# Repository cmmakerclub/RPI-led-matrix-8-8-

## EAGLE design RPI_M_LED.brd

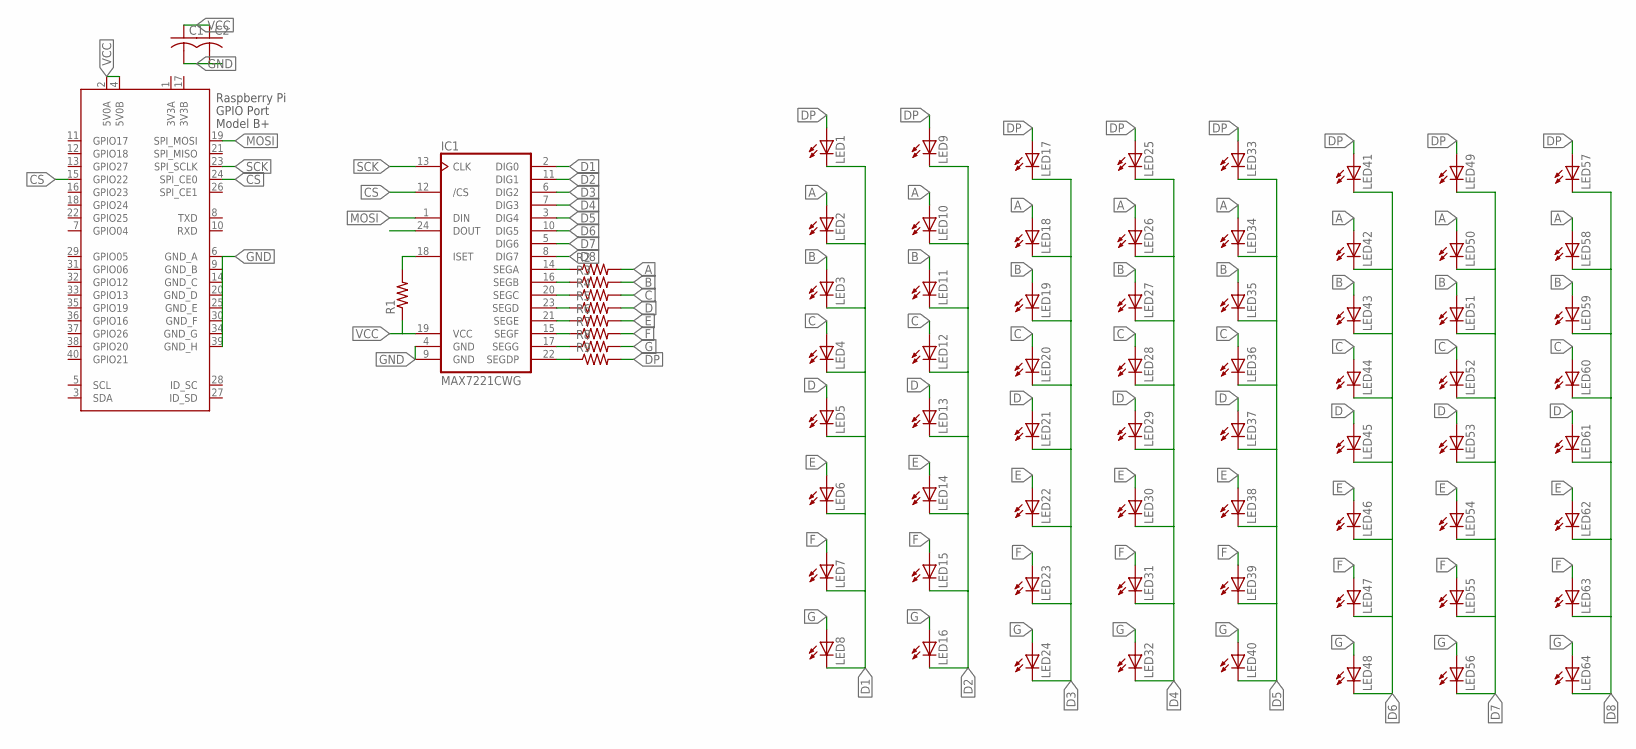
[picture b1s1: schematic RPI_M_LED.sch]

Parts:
C1, C2: C-USC0805; C0805
IC1: MAX7221CWG; SO24W
LED1, LED2, LED3, LED4, LED5, LED6, LED7, LED8, LED9, LED10, LED11, LED12, LED13, LED14, LED15, LED16, LED17, LED18, LED19, LED20, LED21, LED22, LED23, LED24, LED25, LED26, LED27, LED28, LED29, LED30, LED31, LED32, LED33, LED34, LED35, LED36, LED37, LED38, LED39, LED40, LED41, LED42, LED43, LED44, LED45, LED46, LED47, LED48, LED49, LED50, LED51, LED52, LED53, LED54, LED55, LED56, LED57, LED58, LED59, LED60, LED61, LED62, LED63, LED64: LEDCHIPLED_0603; CHIPLED_0603
R1: R-US_R0805; R0805
R2, R3, R4, R5, R6, R7, R8, R9: R-US_R0603; R0603
X1: RASPI_GPIO_B+#_PIN; RASPI_GPIO_B+_PIN

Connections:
3V3A: X1.1 (3V3A)
3V3B: X1.17 (3V3B)
A: LED2.A, LED10.A, LED18.A, LED26.A, LED34.A, LED42.A, LED50.A, LED58.A, R2.2
B: LED3.A, LED11.A, LED19.A, LED27.A, LED35.A, LED43.A, LED51.A, LED59.A, R3.2
C: LED4.A, LED12.A, LED20.A, LED28.A, LED36.A, LED44.A, LED52.A, LED60.A, R4.2
CS: IC1.12 (/CS), X1.15 (GPIO22), X1.24 (SPI_CE0)
D: LED5.A, LED13.A, LED21.A, LED29.A, LED37.A, LED45.A, LED53.A, LED61.A, R5.2
D1: IC1.2 (DIG0), LED1.C, LED2.C, LED3.C, LED4.C, LED5.C, LED6.C, LED7.C, LED8.C
D2: IC1.11 (DIG1), LED9.C, LED10.C, LED11.C, LED12.C, LED13.C, LED14.C, LED15.C, LED16.C
D3: IC1.6 (DIG2), LED17.C, LED18.C, LED19.C, LED20.C, LED21.C, LED22.C, LED23.C, LED24.C
D4: IC1.7 (DIG3), LED25.C, LED26.C, LED27.C, LED28.C, LED29.C, LED30.C, LED31.C, LED32.C
D5: IC1.3 (DIG4), LED33.C, LED34.C, LED35.C, LED36.C, LED37.C, LED38.C, LED39.C, LED40.C
D6: IC1.10 (DIG5), LED41.C, LED42.C, LED43.C, LED44.C, LED45.C, LED46.C, LED47.C, LED48.C
D7: IC1.5 (DIG6), LED49.C, LED50.C, LED51.C, LED52.C, LED53.C, LED54.C, LED55.C, LED56.C
D8: IC1.8 (DIG7), LED57.C, LED58.C, LED59.C, LED60.C, LED61.C, LED62.C, LED63.C, LED64.C
DP: LED1.A, LED9.A, LED17.A, LED25.A, LED33.A, LED41.A, LED49.A, LED57.A, R9.2
E: LED6.A, LED14.A, LED22.A, LED30.A, LED38.A, LED46.A, LED54.A, LED62.A, R6.2
F: LED7.A, LED15.A, LED23.A, LED31.A, LED39.A, LED47.A, LED55.A, LED63.A, R7.2
G: LED8.A, LED16.A, LED24.A, LED32.A, LED40.A, LED48.A, LED56.A, LED64.A, R8.2
GND: C1.2, C2.2, IC1.4 (GND), IC1.9 (GND), X1.6 (GND_A), X1.9 (GND_B), X1.14 (GND_C), X1.20 (GND_D), X1.25 (GND_E), X1.30 (GND_F), X1.34 (GND_G), X1.39 (GND_H)
MOSI: IC1.1 (DIN), X1.19 (SPI_MOSI)
unnamed: IC1.14 (SEGA), R2.1
unnamed: IC1.16 (SEGB), R3.1
unnamed: IC1.20 (SEGC), R4.1
unnamed: IC1.23 (SEGD), R5.1
unnamed: IC1.21 (SEGE), R6.1
unnamed: IC1.18 (ISET), R1.2
unnamed: IC1.15 (SEGF), R7.1
unnamed: IC1.17 (SEGG), R8.1
unnamed: IC1.22 (SEGDP), R9.1
SCK: IC1.13 (CLK), X1.23 (SPI_SCLK)
VCC: C1.1, C2.1, IC1.19 (VCC), R1.1, X1.2 (5V0A), X1.4 (5V0B)

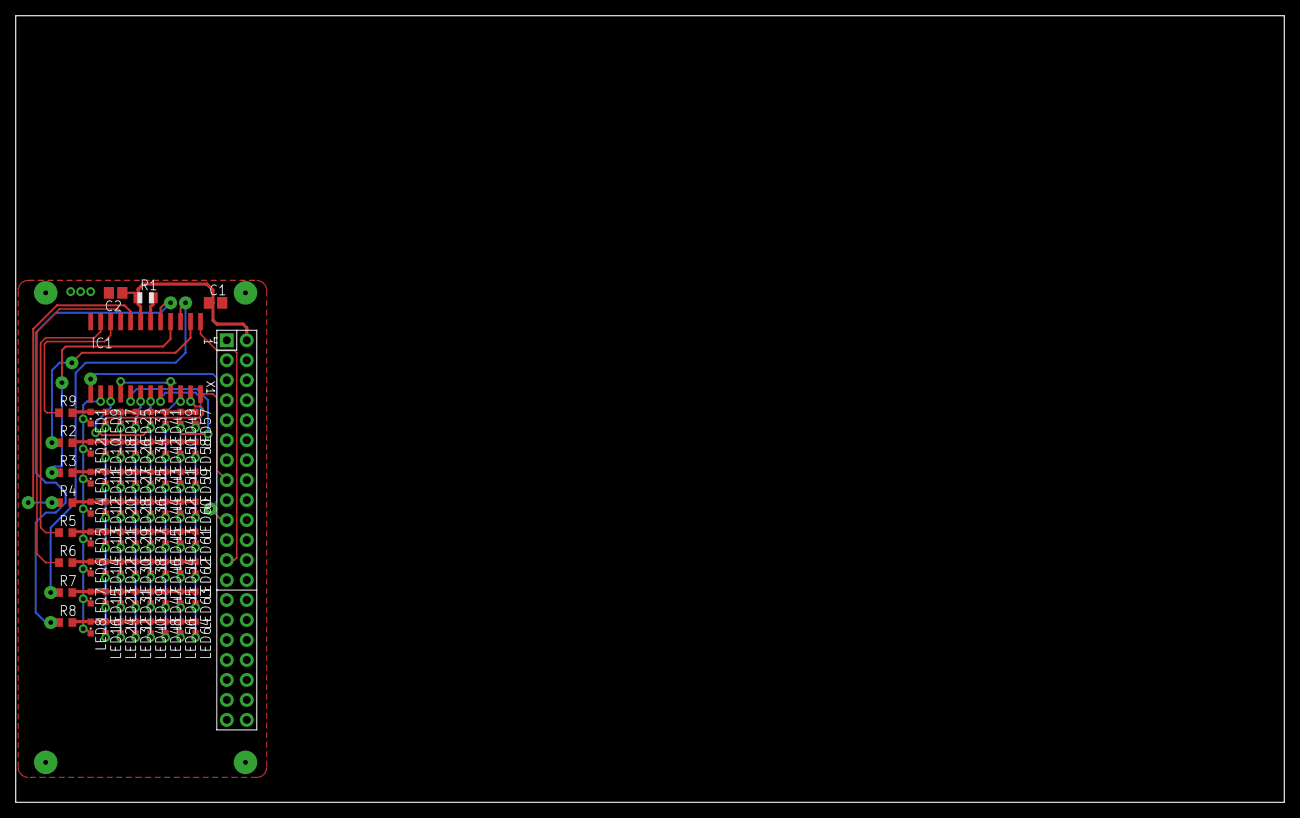
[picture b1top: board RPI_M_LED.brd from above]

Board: 2 copper layers, 161.3 x 100.0 mm, 77 parts (0 on the bottom side), 30 nets.
